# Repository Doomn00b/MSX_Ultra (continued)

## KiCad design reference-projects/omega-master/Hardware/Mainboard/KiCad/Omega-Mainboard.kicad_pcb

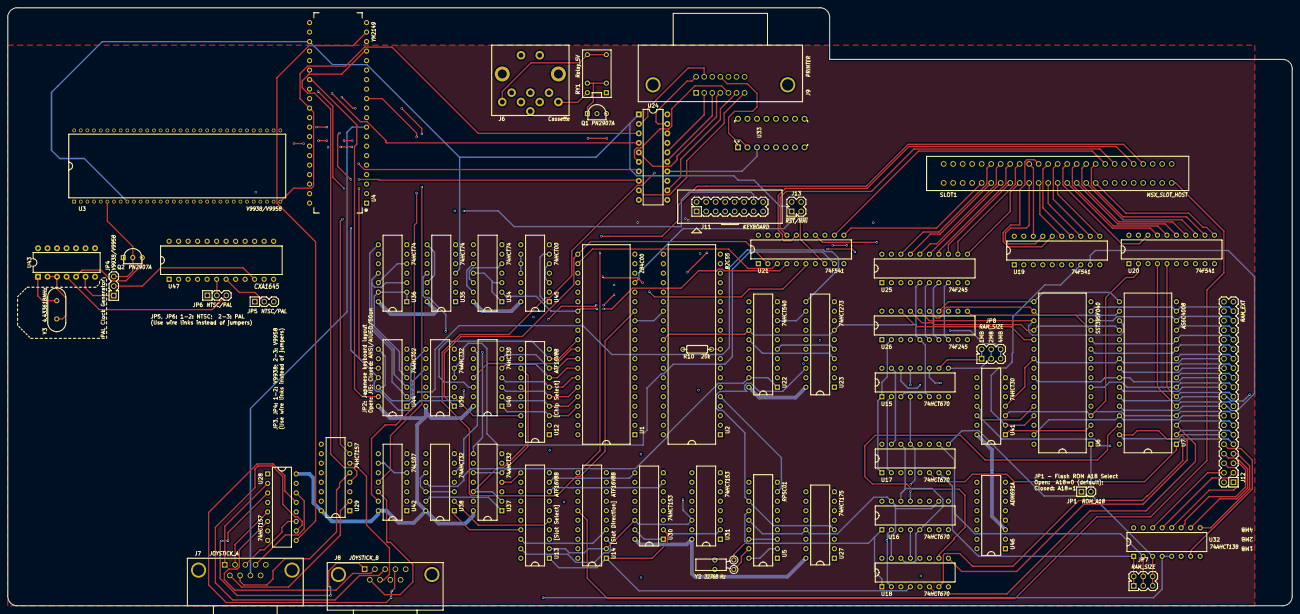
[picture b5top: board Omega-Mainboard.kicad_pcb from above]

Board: 14 copper layers, 343.4 x 159.9 mm, 63 parts (0 on the bottom side), 243 nets.

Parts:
J6: Cassette; Conn_DIN_8pin
J7: JOYSTICK_A; Conn_Dsub_DE9M
J8: JOYSTICK_B; Conn_Dsub_DE9M
J9: PRINTER; Conn_Micro_Ribbon_14F
J11: KEYBOARD; Conn_Pin_Header_8x2_2.54mm
J12: RAM_EXT; Conn_Pin_Header_20x2_2.54mm
J13: ~RST~/~NMI; Conn_Pin_Header_2x2_2.54mm
JP1: ROM_A18; Conn_Pin_Header_2x1_2.54mm
JP4: V9938/V9958; Conn_Pin_Header_3x1_2.54mm
JP5, JP6: NTSC/PAL; Conn_Pin_Header_3x1_2.54mm
JP7, JP8: RAM_SIZE; Conn_Pin_Header_2x3_2.54mm
Q1, Q2: PN2907A; Transistor_TO92_EBC_254
R10: 20k; Res_762
RY1: Relay_5V; Relay_SPDT
SLOT1: MSX_SLOT_HOST; Conn_Edge_50P
U1: Z84C00; IC_DIP40_600
U2: 82C55; IC_DIP40_600
U3: V9938/V9958; IC_SDIP64_600
U4: YM2149; IC_DIP40_600
U5: RP5C01; IC_DIP18_300
U6: SST39SF040; IC_DIP32_600
U7: AS6C4008; IC_DIP32_600
U12, U13, U14: ATF16V8B; IC_DIP20_300
U15, U16, U17, U18: 74HCT670; IC_DIP16_300
U19, U20, U21: 74F541; IC_DIP20_300
U22: 74HCT540; IC_DIP20_300
U23: 74HCT273; IC_DIP20_300
U24: 74HCT273; DIP-20_W7.62mm
U25, U26: 74F245; IC_DIP20_300
U27: 74HCT175; IC_DIP16_300
U28, U29: 74HCT157; IC_DIP16_300
U30, U31: 74HCT153; IC_DIP16_300
U32: 74AHCT138; IC_DIP16_300
U33: SN74AHC125N; TI_PDIP-16_W7.62mm
U34, U35, U36: 74HCT74; IC_DIP14_300
U37, U38, U39: 74AHCT32; IC_DIP14_300
U40, U41: 74HCT30; IC_DIP14_300
U42: 74LS07; IC_DIP14_300
U43: 74HCT04; DIP-14_W7.62mm
U44: 74AHCT02; IC_DIP14_300
U45: 74HCT00; IC_DIP14_300
U46: ADM691A; IC_DIP16_300
U47: CXA1645; IC_DIP24_400
Y2: 32768 Hz; Crystal_32K_Horiz
Y3: 4.433618MHz; Crystal_HC-49U_Vert

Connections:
/A0: J12.31, U1.30, U2.9, U3.29, U6.12, U7.12, U12.9, U15.5, U15.14, U16.5, U16.14, U17.14, U18.14, U19.7, U40.12, U44.9
/A1: J12.29, U1.31, U2.8, U3.28, U6.11, U7.11, U15.4, U15.13, U16.4, U16.13, U17.13, U18.13, U19.6, U40.11, U44.11
/A2: J12.27, U1.32, U6.10, U7.10, U12.8, U19.5, U40.6
/A3: J12.25, U1.33, U6.9, U7.9, U12.7, U19.4, U40.5
/A4: J12.23, U1.34, U6.8, U7.8, U12.6, U19.3, U40.4
/A5: J12.21, U1.35, U6.7, U7.7, U12.5, U19.2, U40.3
/A6: J12.19, U1.36, U6.6, U7.6, U12.4, U20.5, U40.2
/A7: J12.17, U1.37, U6.5, U7.5, U12.3, U20.4, U40.1
/A8: J12.20, U1.38, U6.27, U7.27, U20.3, U41.11
/A9: J12.22, U1.39, U6.26, U7.26, U20.8, U41.5
/A10: J12.28, U1.40, U6.23, U7.23, U20.7, U41.4
/A11: J12.24, U1.1, U6.25, U7.25, U20.6, U41.6
/A12: J12.15, U1.2, U6.4, U7.4, U20.2, U41.3
/A13: J12.18, U1.3, U6.28, U7.28, U19.9, U41.12
/A14: U1.4, U6.29, U13.2, U14.2, U17.5, U18.5, U19.8, U30.14, U31.14, U41.2
/A15: U1.5, U6.3, U13.1, U14.1, U17.4, U18.4, U20.9, U30.2, U31.2, U41.1
/CAS_MOT: Q1.2, U2.13
/CAS_OUT: J6.4, U2.12
/CLK: U3.8, U21.9, U35.11, U39.4, U39.5, U42.5, U42.9
/D0: U1.14, U2.34, U3.40, U4.37, U5.11, U16.3, U16.6, U18.3, U22.18, U23.3, U24.17, U25.9, U26.9, U27.5, U35.2
/D1: U1.15, U2.33, U3.39, U4.36, U5.12, U16.2, U16.7, U18.2, U22.17, U23.18, U24.14, U25.8, U26.8, U27.4, U33.3
/D2: U1.12, U2.32, U3.38, U4.35, U5.13, U16.1, U16.9, U18.1, U22.16, U23.17, U24.4, U25.7, U26.7, U27.12
/D3: U1.8, U2.31, U3.37, U4.34, U5.14, U16.10, U16.15, U18.15, U22.15, U23.4, U24.7, U25.6, U26.6, U27.13
/D4: U1.7, U2.30, U3.36, U4.33, U15.3, U15.6, U17.3, U22.14, U23.7, U24.13, U25.5, U26.5
/D5: JP8.5, JP8.6, U1.9, U2.29, U3.35, U4.32, U15.2, U15.7, U17.2, U22.13, U23.14, U24.8, U25.4, U26.4
/D6: JP8.1, JP8.2, U1.10, U2.28, U3.34, U4.31, U15.10, U15.15, U17.15, U22.12, U23.13, U24.18, U25.3, U26.3
/D7: JP8.3, JP8.4, U1.13, U2.27, U3.32, U4.30, U15.1, U15.9, U17.1, U22.11, U23.8, U24.3, U25.2, U26.2
/KANA_LED: J11.14, U4.6
/KEY_CLICK: R10.2, U2.10
/Memory/MD0: J12.33, U6.13, U7.13, U26.11
/Memory/MD1: J12.35, U6.14, U7.14, U26.12
/Memory/MD2: J12.37, U6.15, U7.15, U26.13
/Memory/MD3: J12.38, U6.17, U7.17, U26.14
/Memory/MD4: J12.36, U6.18, U7.18, U26.15
/Memory/MD5: J12.34, U6.19, U7.19, U26.16
/Memory/MD6: J12.32, U6.20, U7.20, U26.17
/Memory/MD7: J12.30, U6.21, U7.21, U26.18
/Memory/RAM_A14: J12.13, U7.3, U18.6
/Memory/RAM_A15: J12.12, U7.31, U18.7
/Memory/RAM_A16: J12.11, U7.2, U18.9
/Memory/RAM_A17: J12.14, U7.30, U18.10
/Memory/RAM_A18: J12.9, U7.1, U17.6
/Memory/RAM_A19: JP7.1, JP7.2, U17.7, U32.1
/Memory/RAM_A20: JP7.3, JP7.4, U17.10, U32.2
/Memory/RAM_A21: JP7.5, JP7.6, U17.9, U32.3
/Memory/ROM_A18: JP1.2, U6.1
/Memory/~PAGE_RD: U15.11, U16.11, U37.3
/Memory/~PAGE_WR: U15.12, U16.12, U17.12, U18.12, U37.11
/Memory/~RAM0_CS: U7.22, U32.15
/Memory/~RAM1_CS: J12.4, U32.14
/Memory/~RAM2_CS: J12.3, U32.13
/Memory/~RAM3_CS: J12.6, U32.12
/Memory/~RAM4_CS: J12.5, U32.11
/Memory/~RAM5_CS: J12.8, U32.10
/Memory/~RAM6_CS: J12.7, U32.9
/Memory/~RAM7_CS: J12.10, U32.7
/PPI/CAPS_LED: J11.12, U2.11
/PPI/COLUMN0: J11.1, U2.18
/PPI/COLUMN1: J11.3, U2.19
/PPI/COLUMN2: J11.5, U2.20
/PPI/COLUMN3: J11.7, U2.21
/PPI/COLUMN4: J11.9, U2.22
/PPI/COLUMN5: J11.11, U2.23
/PPI/COLUMN6: J11.13, U2.24
/PPI/COLUMN7: J11.15, U2.25
/PPI/ROW_A: J11.4, U2.14
/PPI/ROW_B: J11.6, U2.15
/PPI/ROW_C: J11.8, U2.16
/PPI/ROW_D: J11.10, U2.17
/PPI/SB_SLT_A: U13.6, U31.7
/PPI/SB_SLT_B: U13.7, U31.9
/PPI/SLT_A: U13.8, U30.7
/PPI/SLT_B: U13.9, U30.9
/PPI/~FFFF: U13.5, U38.2, U38.6
/PPI/~SLTSL3: U13.17, U38.1
/PPI/~SUB_RD: U22.1, U22.19, U38.11
/PPI/~SUB_REG_CS: U38.3, U38.10, U38.12
/PPI/~SUB_WR: U23.11, U38.8
/PRT_BUSY: J9.11, U33.2
/PSG/JB0: U4.13, U42.1
/PSG/JB1: U4.12, U42.13
/PSG/JB2: U4.11, U42.11
/PSG/JB3: U4.10, U42.3
/PSG/JOY_BCK: U4.20, U28.7
/PSG/JOY_FWD: U4.21, U28.4
/PSG/JOY_LFT: U4.19, U28.9
/PSG/JOY_OUT_A: J7.8, U4.9
/PSG/JOY_OUT_B: J8.8, U4.8
/PSG/JOY_RGT: U4.18, U28.12
/PSG/JOY_SEL: U4.7, U28.1, U29.1
/PSG/JOY_TRG1: U4.17, U29.4
/PSG/JOY_TRG2: U4.16, U29.7
/PSG/PSG_BC1: U4.29, U44.10
/PSG/PSG_BDIR: U4.27, U44.13
/PSG/~BCK_A: J7.2, U28.5
/PSG/~BCK_B: J8.2, U28.6
/PSG/~FWD_A: J7.1, U28.2
/PSG/~FWD_B: J8.1, U28.3
/PSG/~LFT_A: J7.3, U28.11
/PSG/~LFT_B: J8.3, U28.10
/PSG/~RGT_A: J7.4, U28.14
/PSG/~RGT_B: J8.4, U28.13
/PSG/~TRG1_A: J7.6, U29.2, U42.2
/PSG/~TRG1_B: J8.6, U29.3, U42.12
/PSG/~TRG2_A: J7.7, U29.5, U42.10
/PSG/~TRG2_B: J8.7, U29.6, U42.4
/Processor/PD0: J9.2, U24.16
/Processor/PD1: J9.3, U24.15
/Processor/PD2: J9.4, U24.5
/Processor/PD3: J9.5, U24.6
/Processor/PD4: J9.6, U24.12
/Processor/PD5: J9.7, U24.9
/Processor/PD6: J9.8, U24.19
/Processor/PD7: J9.9, U24.2
/Processor/RTC_VCC: U5.2, U5.18, U46.2
/Processor/~INT: U1.16, U45.8
/Processor/~NMI: J13.3, U1.17
/Processor/~PRT_BSY_RD: U33.1, U37.6
/Processor/~PRT_CMD_CS: U12.13, U37.5, U37.10
/Processor/~PRT_DAT_WR: U12.12, U24.11
/Processor/~PRT_STB_WR: U35.3, U37.8
/Processor/~RTC_AD_WR: U12.17, U27.9
/Processor/~RTC_CS: U12.16, U46.13
/Processor/~RTC_CS_B: U5.1, U46.12
/Processor/~STROBE: J9.1, U35.5
/RESET: U2.35, U46.16
/ROM_A16: U6.2, U13.13
/ROM_A17: U6.30, U13.12
/Slots/BA0: SLOT1.28, U19.13
/Slots/BA1: SLOT1.27, U19.14
/Slots/BA2: SLOT1.30, U19.15
/Slots/BA3: SLOT1.29, U19.16
/Slots/BA4: SLOT1.32, U19.17
/Slots/BA5: SLOT1.31, U19.18
/Slots/BA6: SLOT1.22, U20.15
/Slots/BA7: SLOT1.21, U20.16
/Slots/BA8: SLOT1.24, U20.17
/Slots/BA9: SLOT1.17, U20.12
/Slots/BA10: SLOT1.20, U20.13
/Slots/BA11: SLOT1.19, U20.14
/Slots/BA12: SLOT1.23, U20.18
/Slots/BA13: SLOT1.26, U19.11
/Slots/BA14: SLOT1.25, U19.12
/Slots/BA15: SLOT1.18, U20.11
/Slots/BD0: SLOT1.34, U25.11
/Slots/BD1: SLOT1.33, U25.12
/Slots/BD2: SLOT1.36, U25.13
/Slots/BD3: SLOT1.35, U25.14
/Slots/BD4: SLOT1.38, U25.15
/Slots/BD5: SLOT1.37, U25.16
/Slots/BD6: SLOT1.40, U25.17
/Slots/BD7: SLOT1.39, U25.18
/Slots/B_CLK: SLOT1.42, U21.11
/Slots/SLT_DIR: U14.12, U25.1
/Slots/~B_IORQ: SLOT1.11, U14.8, U21.15
/Slots/~B_M1: SLOT1.9, U14.7, U21.16
/Slots/~B_MREQ: SLOT1.12, U21.14
/Slots/~B_RD: SLOT1.14, U14.9, U21.18
/Slots/~B_RESET: SLOT1.15, U21.12
/Slots/~B_RFSH: SLOT1.6, U21.13
/Slots/~B_WR: SLOT1.13, U21.17
/Slots/~CS1: SLOT1.1, U14.14
/Slots/~CS2: SLOT1.2, U14.15
/Slots/~CS12: SLOT1.3, U14.13
/VDP/CSYNC: JP4.3, Q2.2, U3.6
/VDP/PAL_CLK: JP6.3, U43.4
/VDP/SYNCIN: JP4.2, U47.10
/VDP/~VDP_RD: U3.31, U39.3
/VDP/~VDP_WR: U3.30, U39.11
/~BUSDIR1: SLOT1.10, U14.5
/~IORQ: U1.20, U12.2, U21.5
/~M1: U1.27, U12.11, U21.4, U34.2
/~M1_WAIT: U14.18, U34.5, U34.12
/~MEM_RD: U13.16, U26.1
/~MREQ: U1.19, U13.3, U21.6
/~PAGE_CS: U12.15, U37.2, U37.12
/~PPI_CS: U2.6, U12.14, U45.4
/~PSG_CS: U12.19, U39.9, U44.5, U44.6
/~RAM_SL: U13.15, U32.4, U32.5
/~RD: J12.26, U1.21, U2.5, U5.8, U6.24, U7.24, U13.11, U21.2, U37.1, U37.4, U38.13, U39.1
/~RESET: J13.1, U1.26, U3.9, U4.23, U21.8, U23.1, U24.1, U27.1, U35.4, U45.2, U46.15
/~RFSH: U1.28, U13.4, U21.7
/~ROM_CS: U6.22, U13.14
/~SLTSL1: SLOT1.4, U13.19, U14.3
/~SLTSL2: U13.18, U14.4
/~SLT_INT: SLOT1.8, U45.13
/~SLT_WAIT: SLOT1.7, U14.11
/~VDP_CS: U12.18, U39.2, U39.13
/~VDP_INT: U3.25, U45.12
/~VDP_WAIT: U3.26, U14.17
/~WAIT: U1.24, U14.19
/~WR: J12.16, U1.22, U2.36, U5.10, U6.31, U7.29, U12.1, U21.3, U37.9, U37.13, U38.9, U39.12
GND: U1.29, U2.7, U5.9, U22.10, U23.10, U27.8, U28.8, U29.8, U30.8, U31.8, U34.7, U35.7, U36.7, U37.7, U38.7, U39.7, U40.7, U41.7, U42.7, U44.7, U45.7, U46.4
unnamed: J6.6, RY1.5, RY1.6
unnamed: J6.7, RY1.10
unnamed: JP4.1, U43.6
unnamed: JP5.2, U47.7
unnamed: JP6.1, U39.6
unnamed: JP6.2, U47.6
unnamed: Q1.1, RY1.2, RY1.9
unnamed: Q2.3, U43.5
unnamed: U1.6, U34.1, U34.3, U34.11, U42.8
unnamed: U2.1, U30.11
unnamed: U2.2, U30.5
unnamed: U2.3, U30.10
unnamed: U2.4, U30.6
unnamed: U2.37, U30.13
unnamed: U2.38, U30.3
unnamed: U2.39, U30.12
unnamed: U2.40, U30.4
unnamed: U4.2, U4.5
unnamed: U5.3, U5.16, Y2.1
unnamed: U5.17, Y2.2
unnamed: U22.2, U23.2, U31.6
unnamed: U22.3, U23.19, U31.10
unnamed: U22.4, U23.16, U31.5
unnamed: U22.5, U23.5, U31.11
unnamed: U22.6, U23.6, U31.4
unnamed: U22.7, U23.15, U31.12
unnamed: U22.8, U23.12, U31.3
unnamed: U22.9, U23.9, U31.13
unnamed: U5.5, U27.2
unnamed: U5.4, U27.7
unnamed: U5.6, U27.10
unnamed: U5.7, U27.15
unnamed: U30.1, U30.15, U45.3, U45.5
unnamed: U34.4, U34.9
unnamed: U34.10, U34.13
unnamed: U4.22, U35.9
unnamed: U35.8, U35.12
unnamed: U36.1, U36.2, U36.13, U44.4
unnamed: U36.8, U44.2
unnamed: U36.3, U36.11, U42.6, U44.3
unnamed: U36.5, U36.12
unnamed: U38.4, U41.8
unnamed: U38.5, U40.8
unnamed: U39.8, U44.8, U44.12
unnamed: U39.10, U44.1
unnamed: U43.1, Y3.1
unnamed: U43.2, U43.3, Y3.2
unnamed: U45.1, U45.6
unnamed: U45.9, U45.10, U45.11
VCC: U1.11, U2.26, U22.20, U23.20, U27.16, U28.16, U29.16, U30.16, U31.16, U34.14, U35.14, U36.14, U37.14, U38.14, U39.14, U40.14, U41.14, U42.14, U44.14, U45.14, U46.3
